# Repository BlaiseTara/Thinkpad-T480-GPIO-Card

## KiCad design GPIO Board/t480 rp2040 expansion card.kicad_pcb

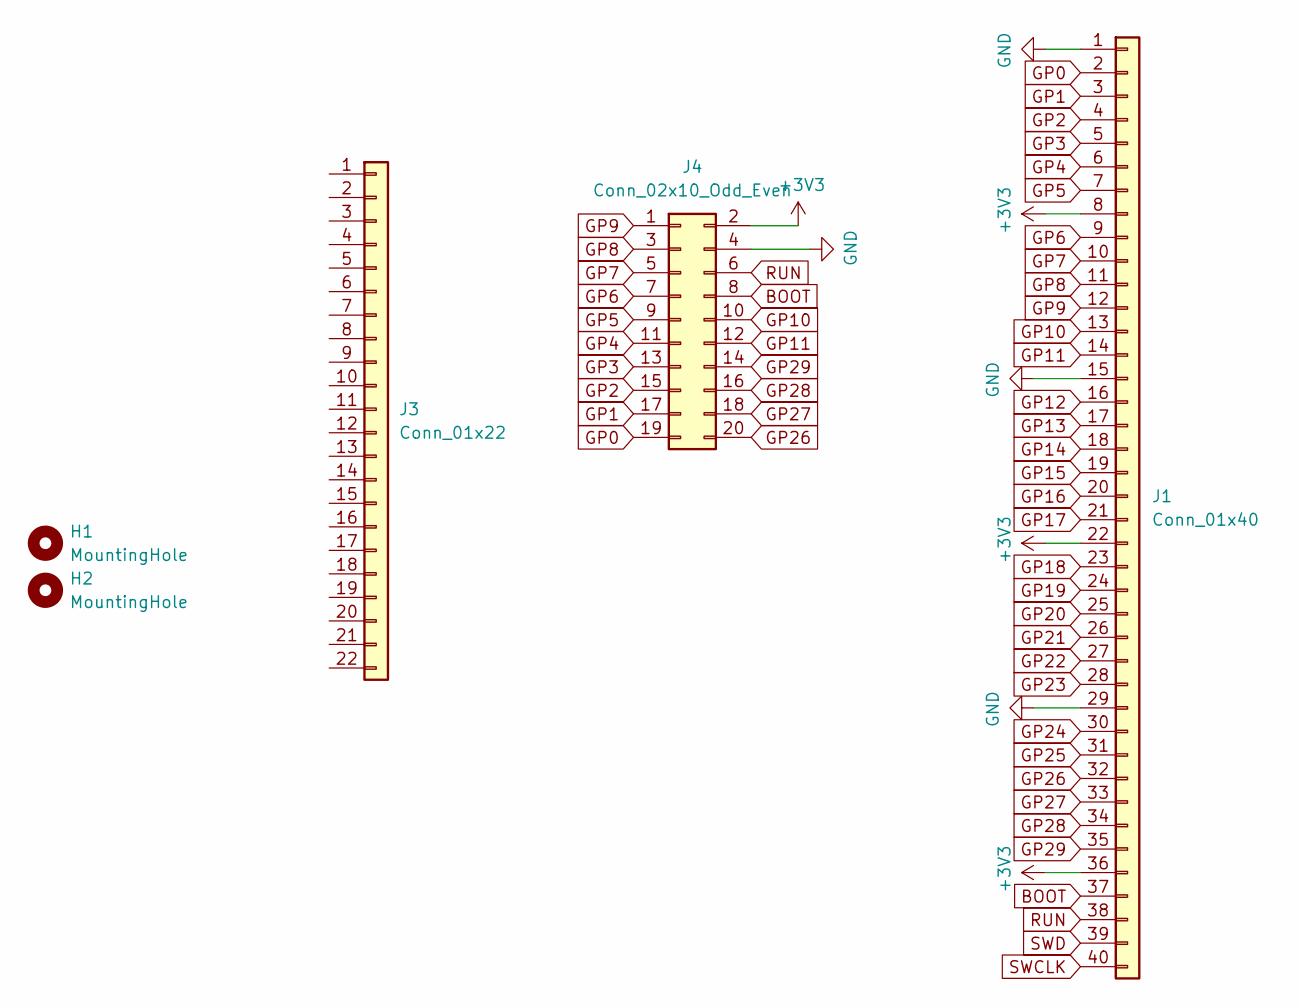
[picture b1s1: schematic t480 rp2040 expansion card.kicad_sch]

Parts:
H1, H2: MountingHole; MountingHole_2.7mm_M2.5_Pad
J1: Conn_01x40; Amphenol_F32Q-1A7x1-11040_1x40-1MP_P0.5mm_Horizontal
J3: Conn_01x22; PinHeader_1x22_P2.54mm_Vertical
J4: Conn_02x10_Odd_Even; PinSocket_2x10_P2.54mm_Vertical

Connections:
+3V3: J1.8, J1.22, J1.36, J4.2
BOOT: J1.37, J4.8
GND: J1.1, J1.15, J1.29, J4.4
GP0: J1.2, J4.19
GP1: J1.3, J4.17
GP2: J1.4, J4.15
GP3: J1.5, J4.13
GP4: J1.6, J4.11
GP5: J1.7, J4.9
GP6: J1.9, J4.7
GP7: J1.10, J4.5
GP8: J1.11, J4.3
GP9: J1.12, J4.1
GP10: J1.13, J4.10
GP11: J1.14, J4.12
GP12: J1.16
GP13: J1.17
GP14: J1.18
GP15: J1.19
GP16: J1.20
GP17: J1.21
GP18: J1.23
GP19: J1.24
GP20: J1.25
GP21: J1.26
GP22: J1.27
GP23: J1.28
GP24: J1.30
GP25: J1.31
GP26: J1.32, J4.20
GP27: J1.33, J4.18
GP28: J1.34, J4.16
GP29: J1.35, J4.14
RUN: J1.38, J4.6
SWCLK: J1.40
SWD: J1.39

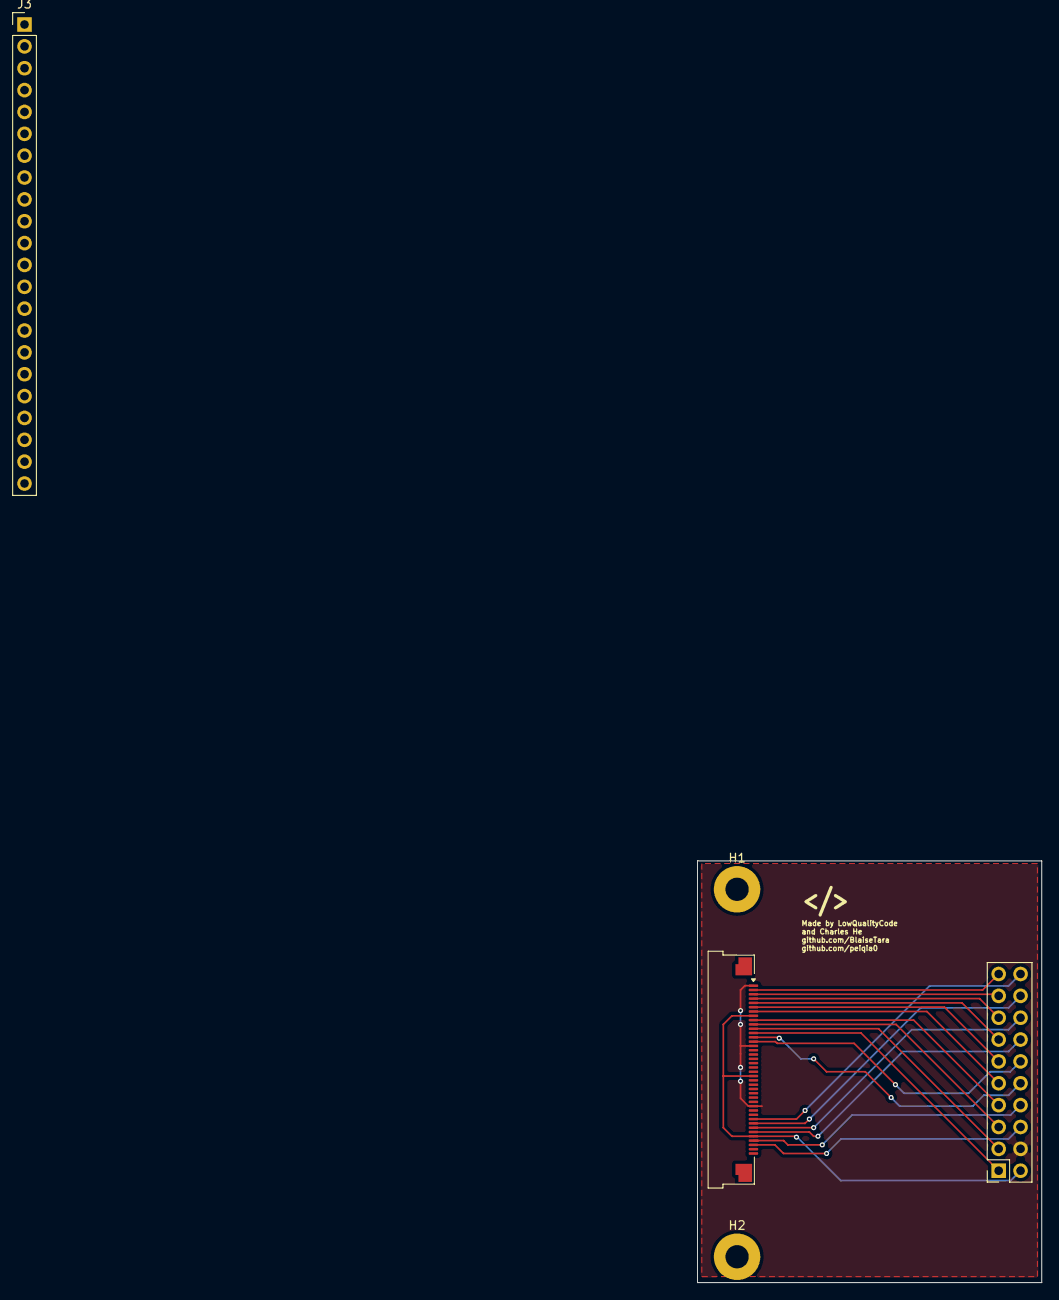
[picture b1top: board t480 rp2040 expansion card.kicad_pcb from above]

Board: 2 copper layers, 40.0 x 49.0 mm, 5 parts (0 on the bottom side), 20 nets.

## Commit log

2026-06-12 Create LICENSE
